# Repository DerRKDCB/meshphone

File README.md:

# Meshphone

A standalone dual-node Meshtastic/MeshCore device built into a Samsung Galaxy A5 form factor.

## Overview

Meshphone is a custom dual-node Meshtastic device featuring:
- Two RAK4630 modules for simultaneous operation with different presets/protocols
- Integrated USB hub for clean connectivity
- 8000mAh 4P 18650 LiPo battery (~48h runtime)
- Samsung Galaxy A5 chassis (€20 eBay find)

## Why Build This?

Off-the-shelf standalone devices like the T-Deck lack the full feature set available in Meshtastic/MeshCore. By making it a dual-node device, I can run two different configurations simultaneously. The nodes connect through a USB hub IC - a cleaner solution than Bluetooth coupling with potential radio interference over short distances.

## Design

### Chassis
The Galaxy A5's internal battery was removed and replaced with external power from the PCB via cables. This allows complete disconnection via switch and increased battery capacity. The phone sits in a cheap TPU case, with 3D printed PLA housing for the nodes and batteries, secured with hot glue.

### Core Components

**RAK4630 Modules** - Chosen for:
- Low power consumption
- Minimal peripheral components
- Integrated USB

Reference designs: RAK4631 and RAK19003 modules.

> **Note:** The RAK USB port requires 5V on VBUS to initialize - learned this during integration and had to bodge it. Fixed in the PCB design.

**Status LEDs (7 total):**
- Charging indicator
- Fully charged indicator
- ON/3.3V OK
- 2x Status Node 1
- 2x Status Node 2

Light channels made from clear PETG filament - works awesome!

**Battery Management:**
- TP4056 + DW01 for charging and protection (classic LiPo charging circuit)
- USB-C charging port on bottom (power only, no data)

**USB Hub - CH334P:**
- First USB project for me
- Chosen for cost and simple reference schematic
- Upstream port centered on PCB
- Phone connects via right-angle USB-C cable
- Pluggable design allows connecting other devices for firmware updates, etc.
- Differential pair routing where possible - USB worked first try!

**3.3V Supply:** TI TPS62203DBVT low-power buck converter

[Schematic PDF](kicad/galaxy_A5_dual_node/galaxy_A5_dual_node.pdf)

### Fixes & Issues

**Bodged during build:**
- USB port didn't activate - forgot 5.1k resistors on CC1/CC2 (fixed in PCB)
- RAK VBUS 5V supply (fixed in PCB)
- Bootloader flash via SWD required for USB drive mode (double-click reset) - used [WisCore RAK4631 Bootloader](https://github.com/oltaco/WisCore_RAK4631_Bootloader)

**Remaining issue:**
When switching on either node, the hub disconnects and reconnects completely, making it impossible to differentiate which node is which USB device. Not sure why this happens, but it's manageable.

## Documentation

- [Component references and links](notes.md)
- [KiCad PCB files](kicad/galaxy_A5_dual_node/)
- [FreeCAD 3D models](freecad/)

## Final Thoughts

This project was an awesome learning experience and I love the result. For future versions I'd do some things differently - most likely keeping the battery in the phone and supplying the whole PCB from the phone's USB port.

## Images

by DerRKDCB

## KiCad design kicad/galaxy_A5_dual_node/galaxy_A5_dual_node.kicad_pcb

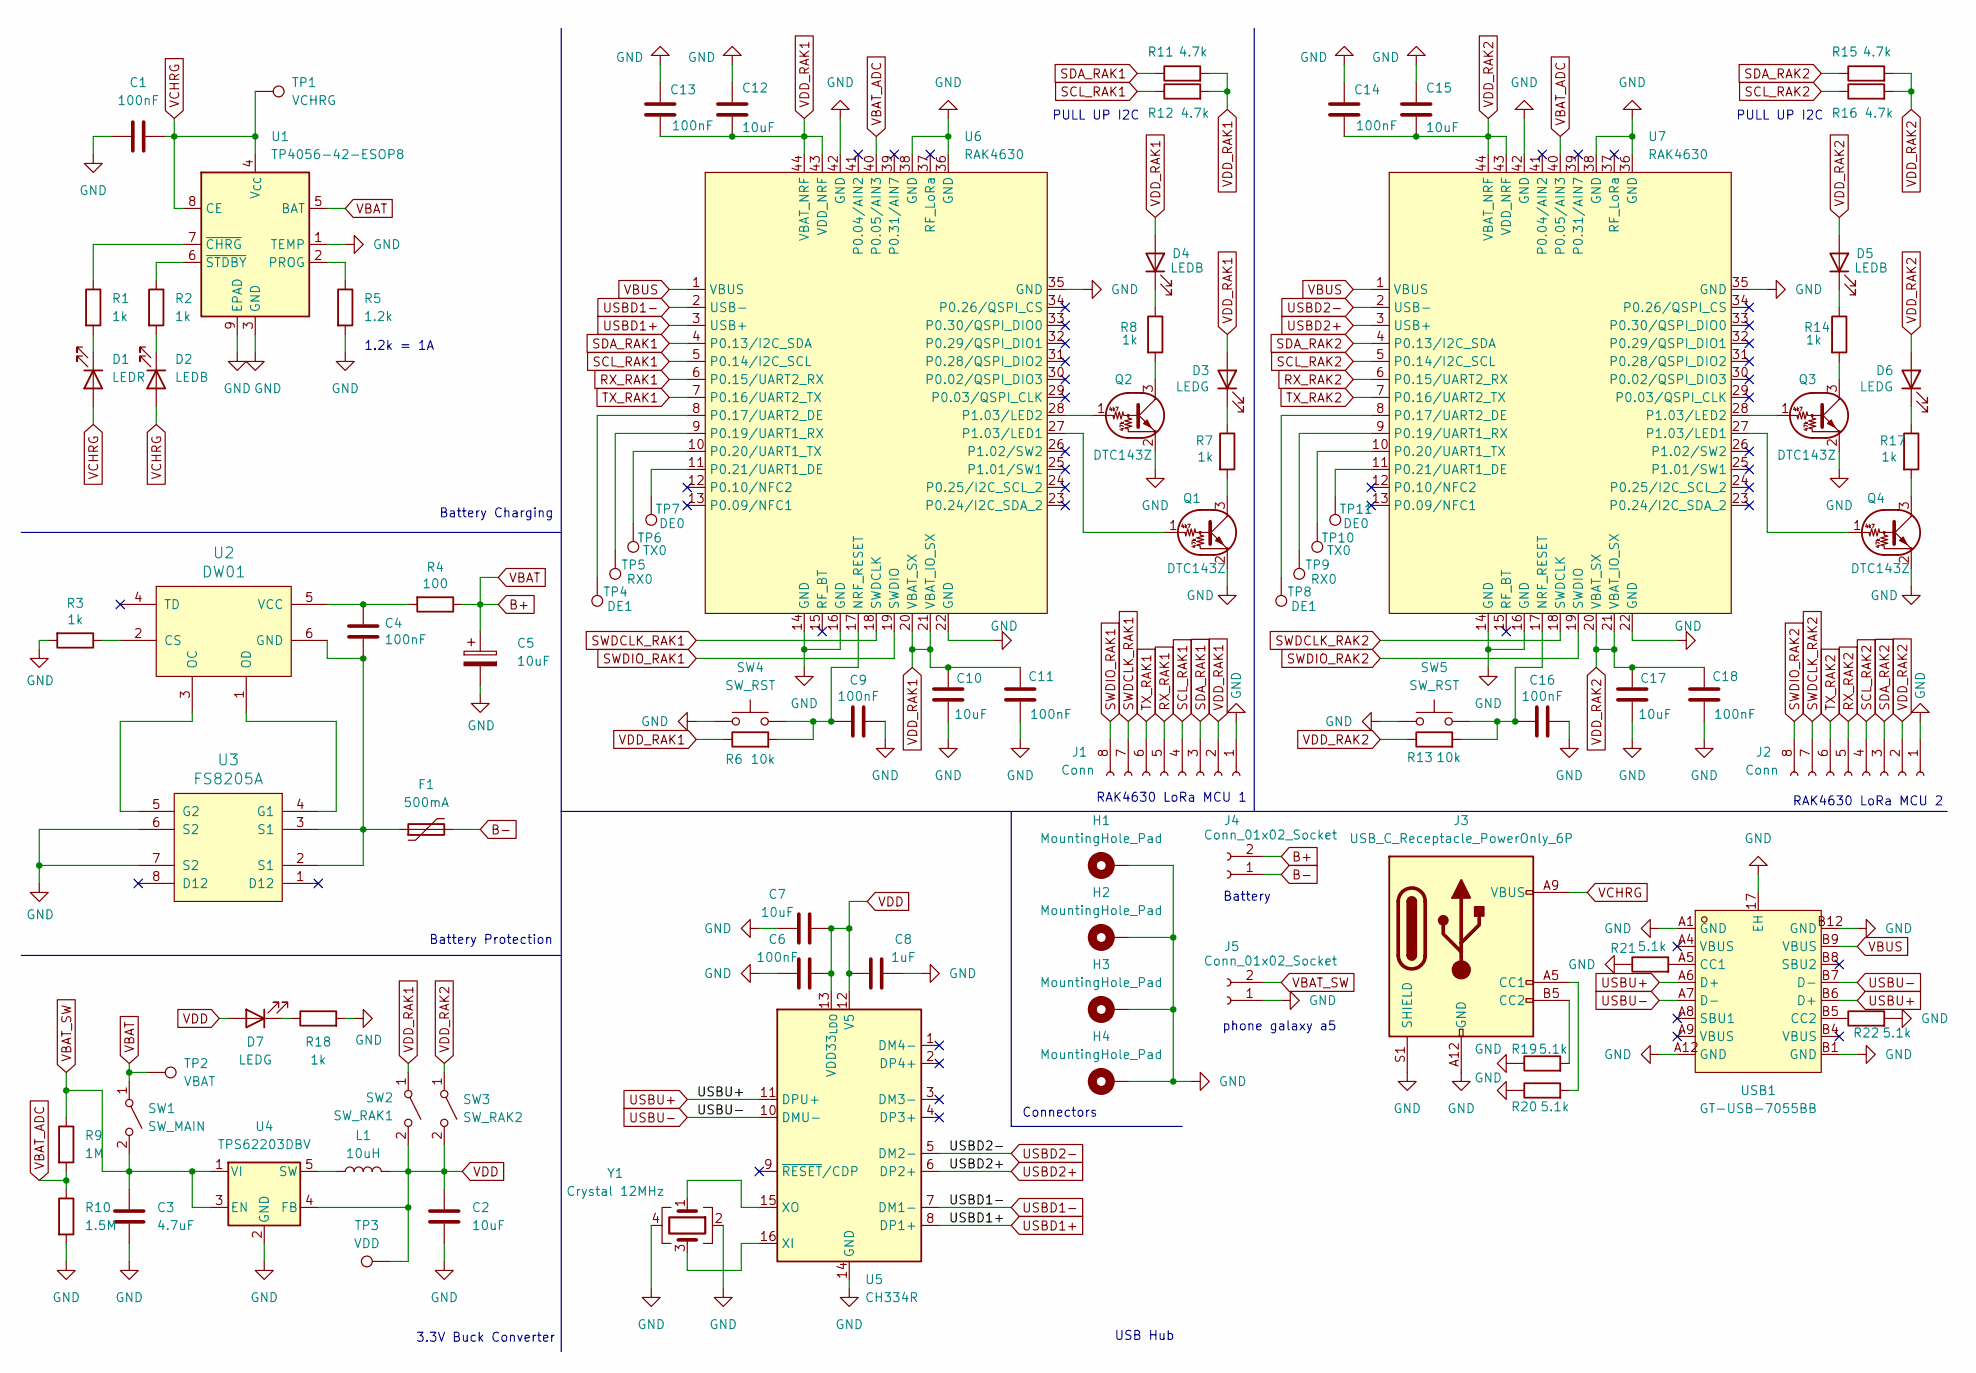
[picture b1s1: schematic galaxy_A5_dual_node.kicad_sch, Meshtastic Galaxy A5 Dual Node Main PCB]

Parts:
C1, C4, C6, C9, C11, C13, C14, C16, C18: 100nF; C_0805_2012Metric
C2, C7, C10, C12, C15, C17: 10uF; C_0805_2012Metric
C3: 4.7uF; C_0805_2012Metric
C5: 10uF; CP_EIA-3216-12_Kemet-S
C8: 1uF; C_0805_2012Metric
D1: LEDR; LED_0805_2012Metric
D2, D4, D5: LEDB; LED_0805_2012Metric
D3, D6, D7: LEDG; LED_0805_2012Metric
F1: 500mA; Fuse_1812_4532Metric_Pad1.30x3.40mm_HandSolder
H1, H2, H3, H4: MountingHole_Pad; MountingHole_2.2mm_M2_DIN965_Pad_TopBottom
J1, J2: Conn; PinHeader_1x08_P2.54mm_Vertical
J3: USB_C_Receptacle_PowerOnly_6P; USB_C_Receptacle_GCT_USB4125-xx-x_6P_TopMnt_Horizontal
J4, J5: Conn_01x02_Socket; JST_XH_B2B-XH-A_1x02_P2.50mm_Vertical
L1: 10uH; L_APV_ANR4018
Q1, Q2, Q3, Q4: DTC143Z; SOT-23
R1, R2, R3, R7, R8, R14, R17, R18: 1k; R_0805_2012Metric
R4: 100; R_0805_2012Metric
R5: 1.2k; R_0805_2012Metric
R6, R13: 10k; R_0805_2012Metric
R9: 1M; R_0805_2012Metric
R10: 1.5M; R_0805_2012Metric
R11, R12, R15, R16: 4.7k; R_0805_2012Metric
R19, R20, R21, R22: 5.1k; R_0805_2012Metric
SW1: SW_MAIN; SW_Slide_SPDT_Angled_CK_OS102011MA1Q
SW2: SW_RAK1; SW_Slide_SPDT_Angled_CK_OS102011MA1Q
SW3: SW_RAK2; SW_Slide_SPDT_Angled_CK_OS102011MA1Q
SW4, SW5: SW_RST; SW_PUSH_6mm_H5mm
TP1: VCHRG; TestPoint_Pad_D1.5mm
TP2: VBAT; TestPoint_Pad_D1.5mm
TP3: VDD; TestPoint_Pad_D1.5mm
TP4, TP8: DE1; TestPoint_Pad_D1.5mm
TP5, TP9: RX0; TestPoint_Pad_D1.5mm
TP6, TP10: TX0; TestPoint_Pad_D1.5mm
TP7, TP11: DE0; TestPoint_Pad_D1.5mm
U1: TP4056-42-ESOP8; SOIC-8-1EP_3.9x4.9mm_P1.27mm_EP2.41x3.3mm_ThermalVias
U2: DW01; SOT-23-6
U3: FS8205A; TSSOP-8_4.4x3mm_P0.65mm
U4: TPS62203DBV; SOT-23-5
U5: CH334R; QSOP-16_3.9x4.9mm_P0.635mm
U6, U7: RAK4630; rak4630
USB1: GT-USB-7055BB; USB-C-TH_GT-USB-7055BB; LCSC Part C7450621
Y1: Crystal 12MHz; Crystal_SMD_3225-4Pin_3.2x2.5mm_HandSoldering

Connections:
B+: C5.1, J4.2, R4.1, SW1.1 (A), TP2.1 (1_1), U1.5 (BAT)
B-: F1.2, J4.1
GND: C1.1, C2.2, C3.2, C5.2, C6.1, C7.1, C8.2, C9.2, C10.2, C11.2, C12.1, C13.1, C14.1, C15.1, C16.2, C17.2, C18.2, H1.1 (1_1), H2.1 (1_1), H3.1 (1_1), H4.1 (1_1), J1.1, J2.1, J3.A12 (GND), J3.B12 (GND), J3.S1 (SHIELD), J5.1, Q1.2 (E), Q2.2 (E), Q3.2 (E), Q4.2 (E), R3.2, R5.2, R10.2, R18.2, R19.1, R20.1, R21.1, R22.2, SW4.1, SW5.1, U1.1 (TEMP), U1.3 (GND), U1.9 (EPAD), U3.6 (S2), U3.7 (S2), U4.2 (GND), U5.14 (GND), U6.14 (GND), U6.16 (GND), U6.22 (GND), U6.35 (GND), U6.36 (GND), U6.38 (GND), U6.42 (GND), U7.14 (GND), U7.16 (GND), U7.22 (GND), U7.35 (GND), U7.36 (GND), U7.38 (GND), U7.42 (GND), USB1.17 (EH), USB1.A1 (GND), USB1.A12 (GND), USB1.B1 (GND), USB1.B12 (GND), Y1.2, Y1.4
unnamed: D1.1 (K), R1.2
unnamed: D2.1 (K), R2.2
unnamed: D3.1 (K), R7.1
unnamed: D4.1 (K), R8.1
unnamed: D5.1 (K), R14.1
unnamed: D6.1 (K), R17.1
unnamed: D7.1 (K), R18.1
unnamed: J3.A5 (CC1), R20.2
unnamed: J3.B5 (CC2), R19.2
unnamed: Q1.1 (B), U6.27 (P1.03/LED1)
unnamed: Q1.3 (C), R7.2
unnamed: Q2.1 (B), U6.28 (P1.03/LED2)
unnamed: Q2.3 (C), R8.2
unnamed: Q3.1 (B), U7.28 (P1.03/LED2)
unnamed: Q3.3 (C), R14.2
unnamed: Q4.1 (B), U7.27 (P1.03/LED1)
unnamed: Q4.3 (C), R17.2
unnamed: R5.1, U1.2 (PROG)
unnamed: R1.1, U1.7 (~CHRG)
unnamed: R2.1, U1.6 (~STDBY)
unnamed: R3.1, U2.2 (CS)
unnamed: C4.2, F1.1, U2.6 (GND), U3.2 (S1), U3.3 (S1)
unnamed: U2.3 (OC), U3.5 (G2)
unnamed: U2.1 (OD), U3.4 (G1)
unnamed: C4.1, R4.2, U2.5 (VCC)
unnamed: L1.1, U4.5 (SW)
unnamed: U5.16 (XI), Y1.3
unnamed: U5.15 (XO), Y1.1
unnamed: C9.1, R6.2, SW4.2, U6.17 (NRF_RESET)
unnamed: TP4.1 (1_1), U6.8 (P0.17/UART2_DE)
unnamed: TP5.1 (1_1), U6.9 (P0.19/UART1_RX)
unnamed: TP6.1 (1_1), U6.10 (P0.20/UART1_TX)
unnamed: TP7.1 (1_1), U6.11 (P0.21/UART1_DE)
unnamed: C16.1, R13.2, SW5.2, U7.17 (NRF_RESET)
unnamed: TP8.1 (1_1), U7.8 (P0.17/UART2_DE)
unnamed: TP9.1 (1_1), U7.9 (P0.19/UART1_RX)
unnamed: TP10.1 (1_1), U7.10 (P0.20/UART1_TX)
unnamed: TP11.1 (1_1), U7.11 (P0.21/UART1_DE)
unnamed: R21.2, USB1.A5 (CC1)
unnamed: R22.1, USB1.B5 (CC2)
RX_RAK1: J1.5, U6.6 (P0.15/UART2_RX)
RX_RAK2: J2.5, U7.6 (P0.15/UART2_RX)
SCL_RAK1: J1.4, R12.1, U6.5 (P0.14/I2C_SCL)
SCL_RAK2: J2.4, R16.1, U7.5 (P0.14/I2C_SCL)
SDA_RAK1: J1.3, R11.1, U6.4 (P0.13/I2C_SDA)
SDA_RAK2: J2.3, R15.1, U7.4 (P0.13/I2C_SDA)
SWDCLK_RAK1: J1.7, U6.18 (SWDCLK)
SWDCLK_RAK2: J2.7, U7.18 (SWDCLK)
SWDIO_RAK1: J1.8, U6.19 (SWDIO)
SWDIO_RAK2: J2.8, U7.19 (SWDIO)
TX_RAK1: J1.6, U6.7 (P0.16/UART2_TX)
TX_RAK2: J2.6, U7.7 (P0.16/UART2_TX)
USBD1+: U5.8 (DP1+), U6.3 (USB+)
USBD1-: U5.7 (DM1-), U6.2 (USB-)
USBD2+: U5.6 (DP2+), U7.3 (USB+)
USBD2-: U5.5 (DM2-), U7.2 (USB-)
USBU+: U5.11 (DPU+), USB1.A6 (D+), USB1.B6 (D+)
USBU-: U5.10 (DMU-), USB1.A7 (D-), USB1.B7 (D-)
VBAT_ADC: R9.2, R10.1, U6.40 (P0.05/AIN3), U7.40 (P0.05/AIN3)
VBAT_SW: C3.1, J5.2, R9.1, SW1.2 (B), U4.1 (VI), U4.3 (EN)
VBUS: U6.1 (VBUS), U7.1 (VBUS), USB1.B9 (VBUS)
VCHRG: C1.2, D1.2 (A), D2.2 (A), J3.A9 (VBUS), J3.B9 (VBUS), TP1.1 (1_1), U1.4 (V_{CC}), U1.8 (CE)
VDD: C2.1, C6.2, C7.2, C8.1, D7.2 (A), L1.2, SW2.2 (B), SW3.2 (B), TP3.1 (1_1), U4.4 (FB), U5.12 (V5), U5.13 (VDD33_{LDO})
VDD_RAK1: C10.1, C11.1, C12.2, C13.2, D3.2 (A), D4.2 (A), J1.2, R6.1, R11.2, R12.2, SW2.1 (A), U6.20 (VBAT_SX), U6.21 (VBAT_IO_SX), U6.43 (VDD_NRF), U6.44 (VBAT_NRF)
VDD_RAK2: C14.2, C15.2, C17.1, C18.1, D5.2 (A), D6.2 (A), J2.2, R13.1, R15.2, R16.2, SW3.1 (A), U7.20 (VBAT_SX), U7.21 (VBAT_IO_SX), U7.43 (VDD_NRF), U7.44 (VBAT_NRF)

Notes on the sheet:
PULL UP I2C
phone galaxy a5
RAK4630 LoRa MCU 2
Battery Protection
3.3V Buck Converter
Battery Charging
Connectors
USB Hub
Battery
1.2k = 1A
RAK4630 LoRa MCU 1

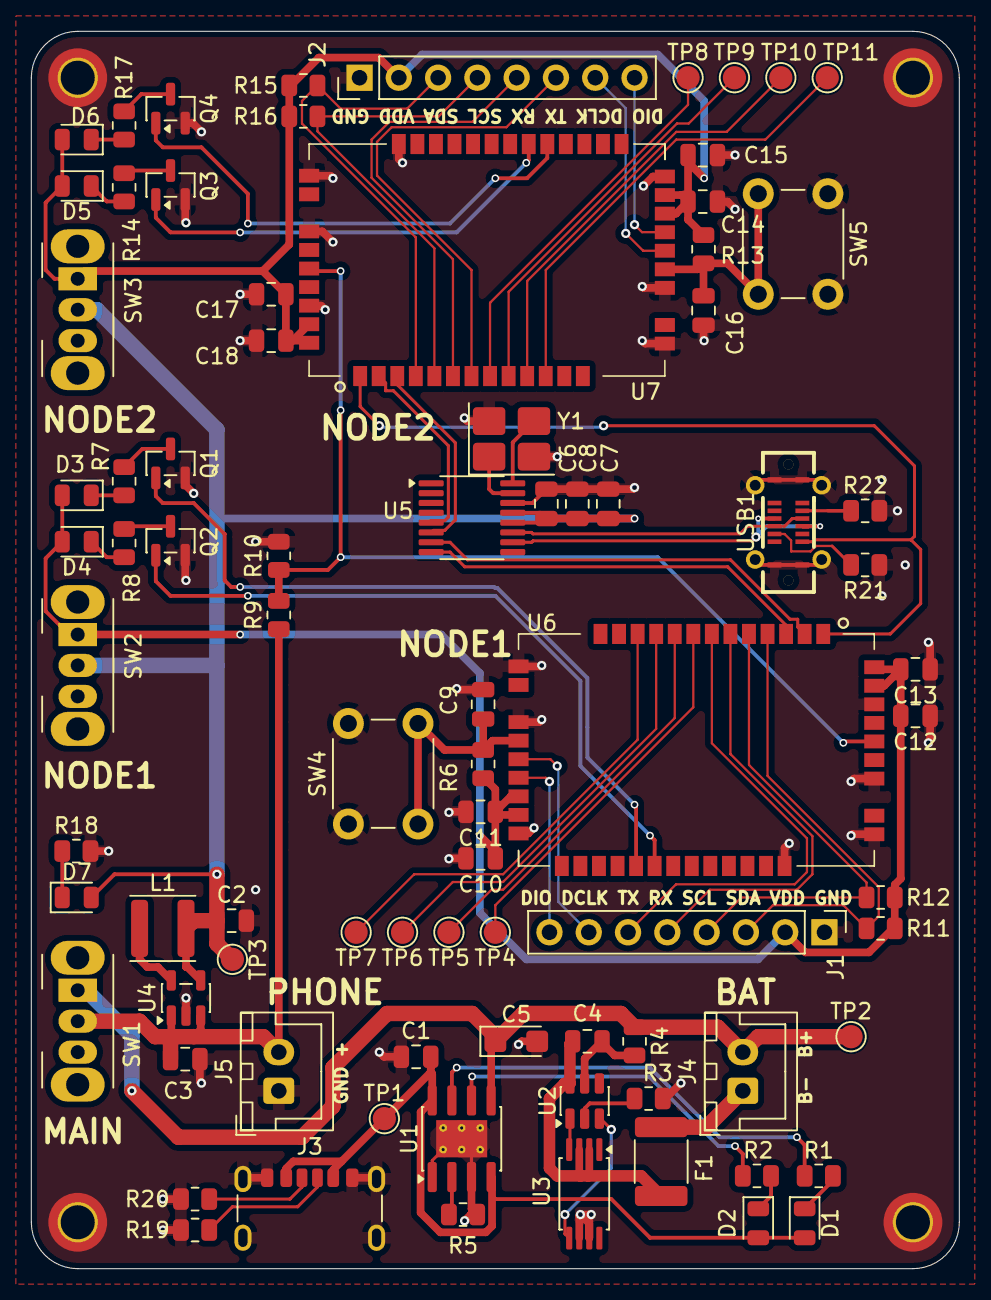
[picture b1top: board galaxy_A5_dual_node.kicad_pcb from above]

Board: 2 copper layers, 60.0 x 80.0 mm, 87 parts (0 on the bottom side), 68 nets.

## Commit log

2026-04-30 add readme
2026-04-30 Removed unwanted files marked in .gitignore
2026-04-30 cleanup freecad
2026-04-30 cleanup and export block diagram
2026-04-30 add block diagram image
2026-04-30 add images
2026-04-30 add readme contents
2026-04-30 update Documentation section
2026-04-30 fixed USB CC, VBUS RAK
2026-04-30 kicad history gitignore
2026-05-03 update pcb version number
2026-05-03 Add missing image to README
